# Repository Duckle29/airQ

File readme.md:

# AirQ

This is a small PCB meant to work with a WEMOS S2.  
All sensors should work if using a D1 mini, but the display won't

This takes:  

- Sensair S8 CO2 sensor
- BME680 breakout board for pressure, temperature, humidity, and VOC
- SDS011 particle counting sensor
- A 2.2" ILI9341 LCD. (S2 mini only)

and connects it all to a WeMOS S2 mini (or D1 mini sans LCD)

Everything is meant to bolt or solder to the PCB, making packaging easier.

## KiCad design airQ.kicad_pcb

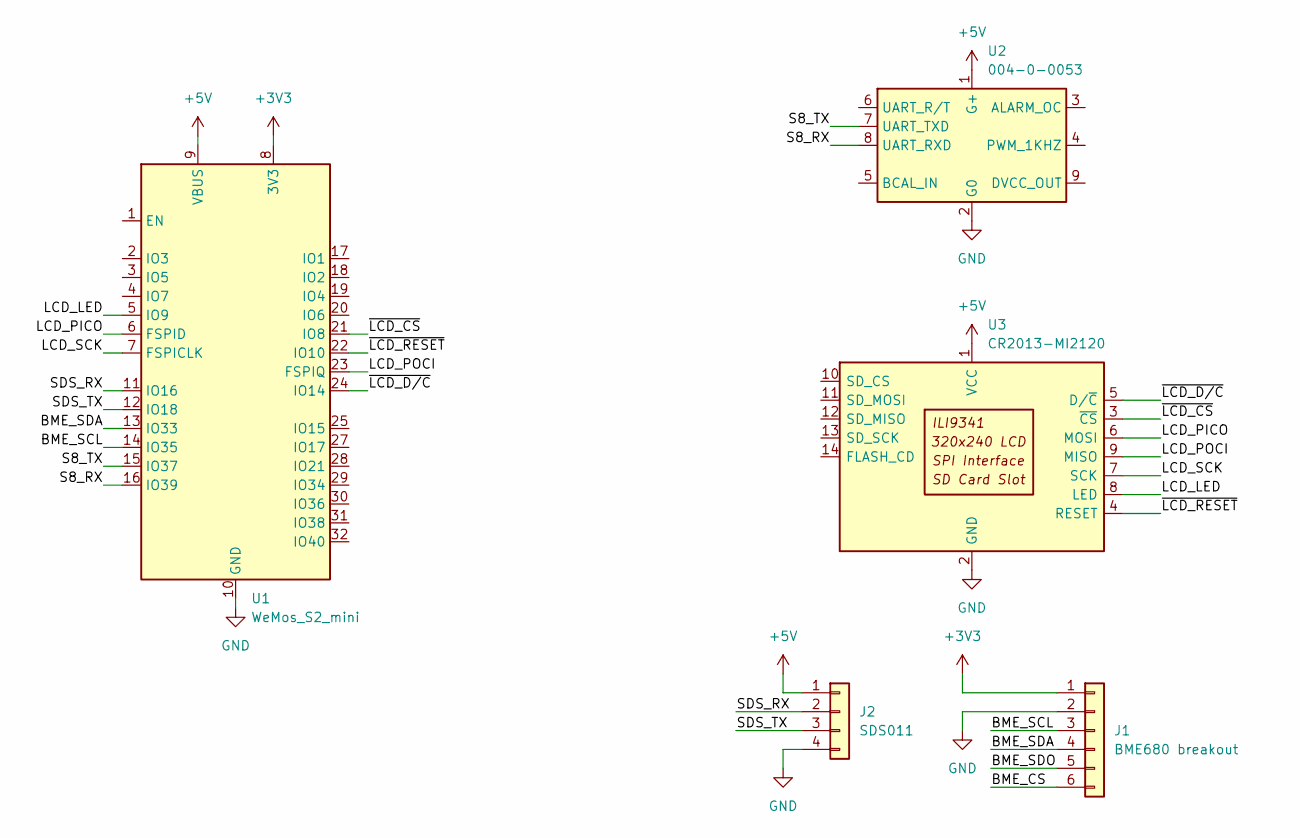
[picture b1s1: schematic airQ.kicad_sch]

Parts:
J1: BME680 breakout; PinHeader_1x06_P2.54mm_Vertical
J2: SDS011; JST_XH_B4B-XH-AM_1x04_P2.50mm_Vertical
U1: WeMos_S2_mini; WEMOS_S2_mini
U2: 004-0-0053; Senseair_S8_Up
U3: CR2013-MI2120

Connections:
+3V3: J1.1, U1.8 (3V3)
+5V: J2.1, U1.9 (VBUS), U2.1 (G+), U3.1 (VCC)
/BME_CS: J1.6
/BME_SCL: J1.3, U1.14 (IO35)
/BME_SDA: J1.4, U1.13 (IO33)
/BME_SDO: J1.5
/LCD_LED: U1.5 (IO9), U3.8 (LED)
/LCD_PICO: U1.6 (FSPID), U3.6 (MOSI)
/LCD_POCI: U1.23 (FSPIQ), U3.9 (MISO)
/LCD_SCK: U1.7 (FSPICLK), U3.7 (SCK)
/S8_RX: U1.16 (IO39), U2.8 (UART_RXD)
/S8_TX: U1.15 (IO37), U2.7 (UART_TXD)
/SDS_RX: J2.2, U1.11 (IO16)
/SDS_TX: J2.3, U1.12 (IO18)
/~LCD_CS: U1.21 (IO8), U3.3 (~CS)
/~LCD_D/C: U1.24 (IO14), U3.5 (D/~C)
/~LCD_RESET: U1.22 (IO10), U3.4 (RESET)
GND: J1.2, J2.4, U1.10 (GND), U1.26 (GND), U2.2 (G0), U3.2 (GND)

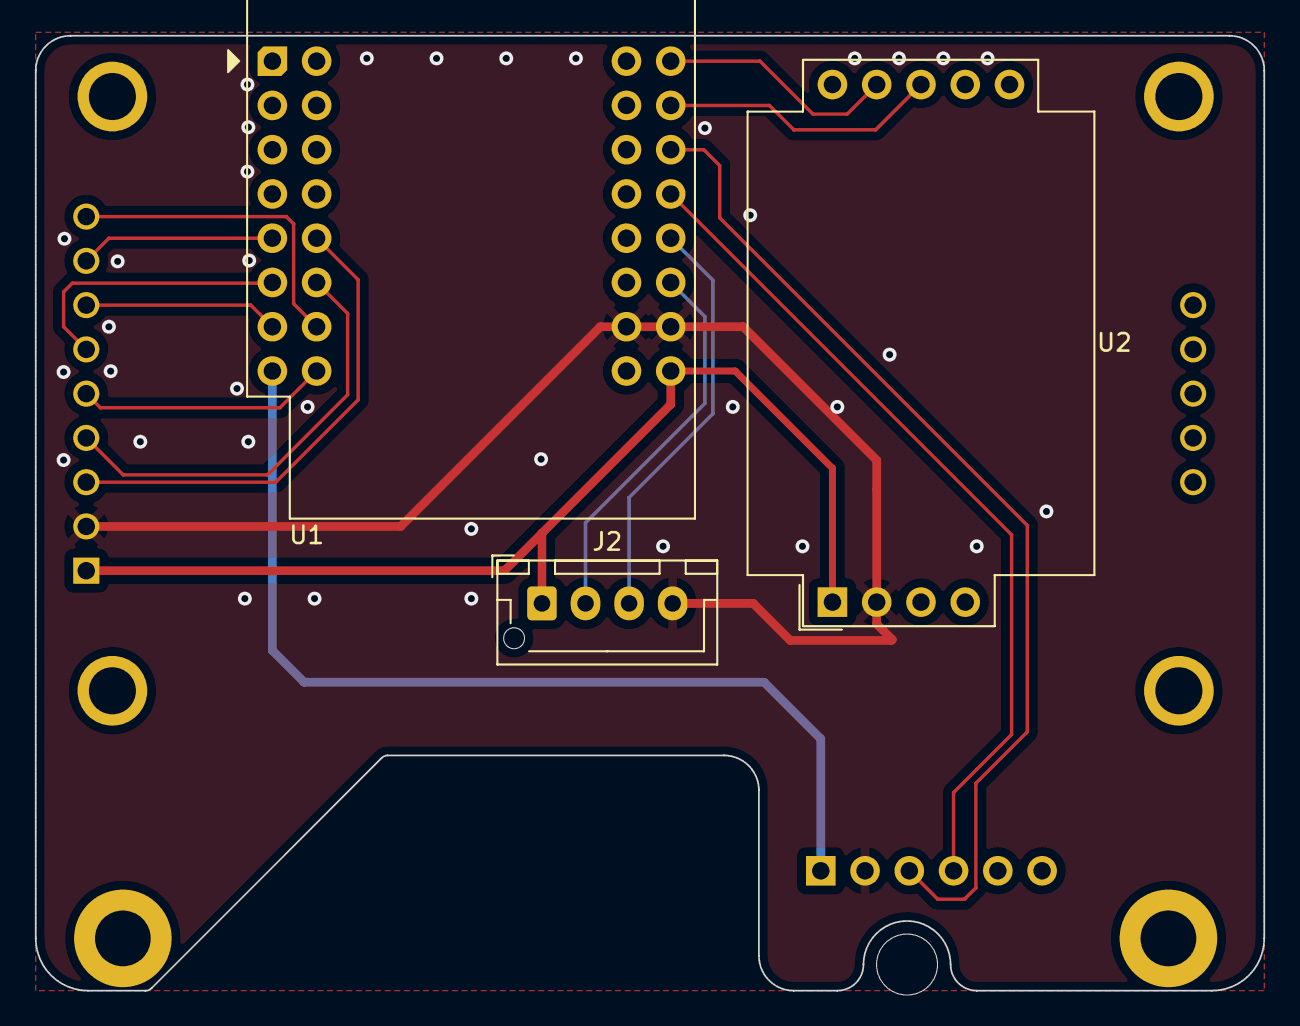
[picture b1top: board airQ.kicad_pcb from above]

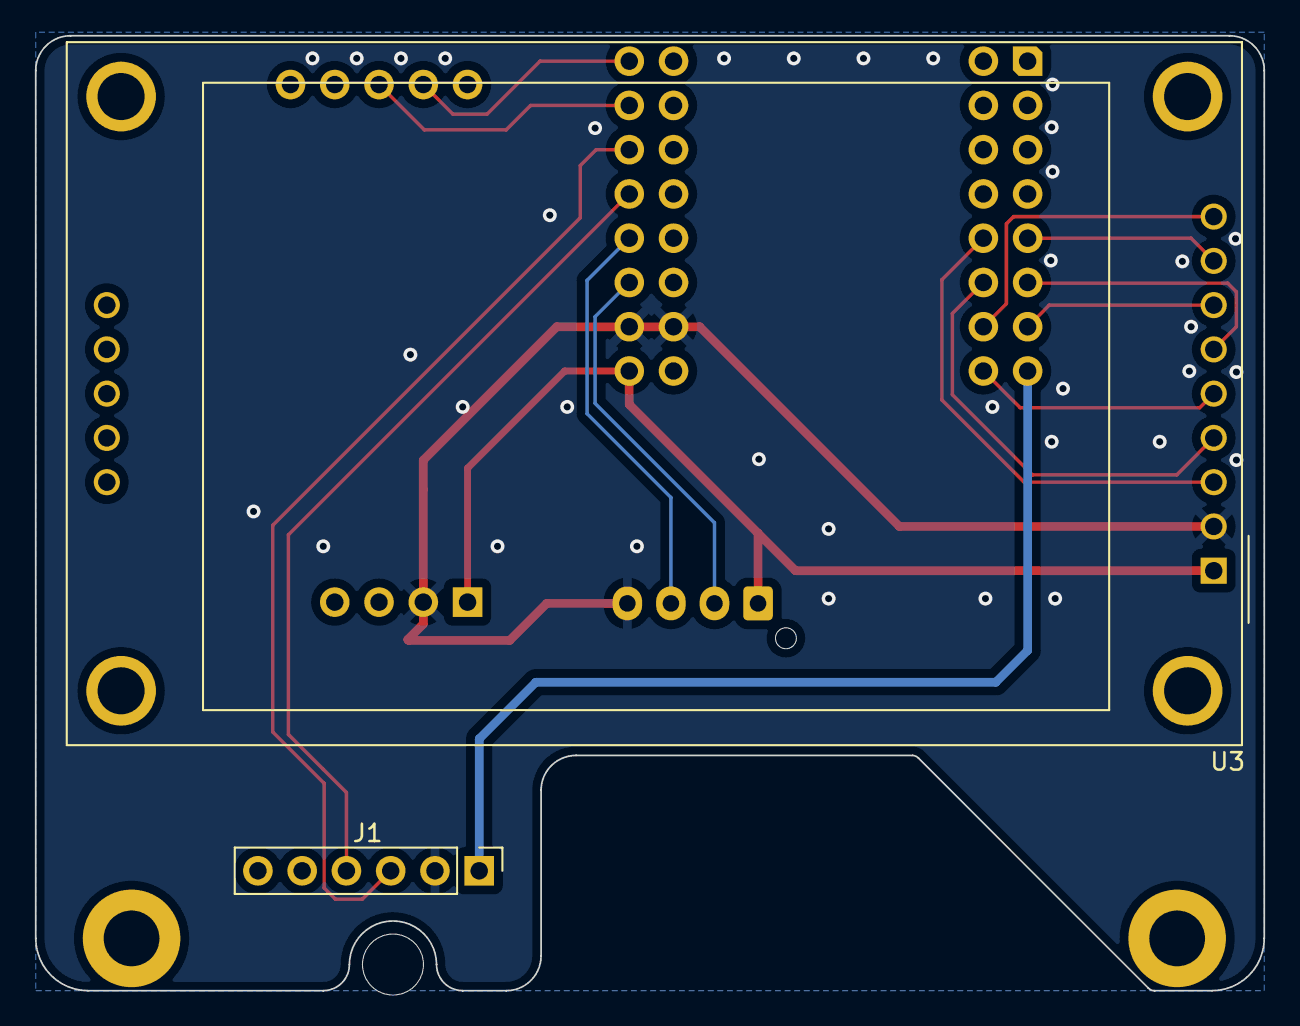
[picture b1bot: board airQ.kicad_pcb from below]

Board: 2 copper layers, 70.5 x 54.8 mm, 5 parts (2 on the bottom side), 16 nets.
